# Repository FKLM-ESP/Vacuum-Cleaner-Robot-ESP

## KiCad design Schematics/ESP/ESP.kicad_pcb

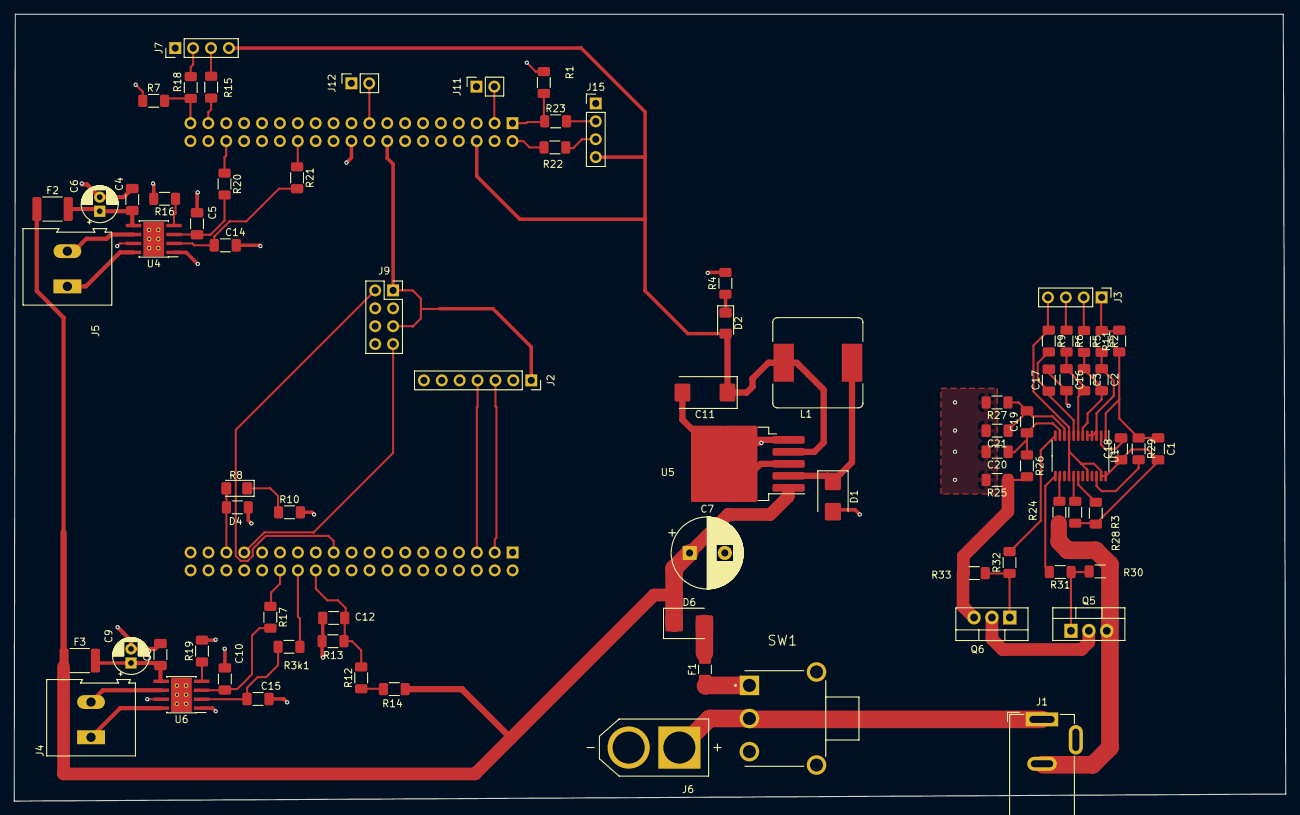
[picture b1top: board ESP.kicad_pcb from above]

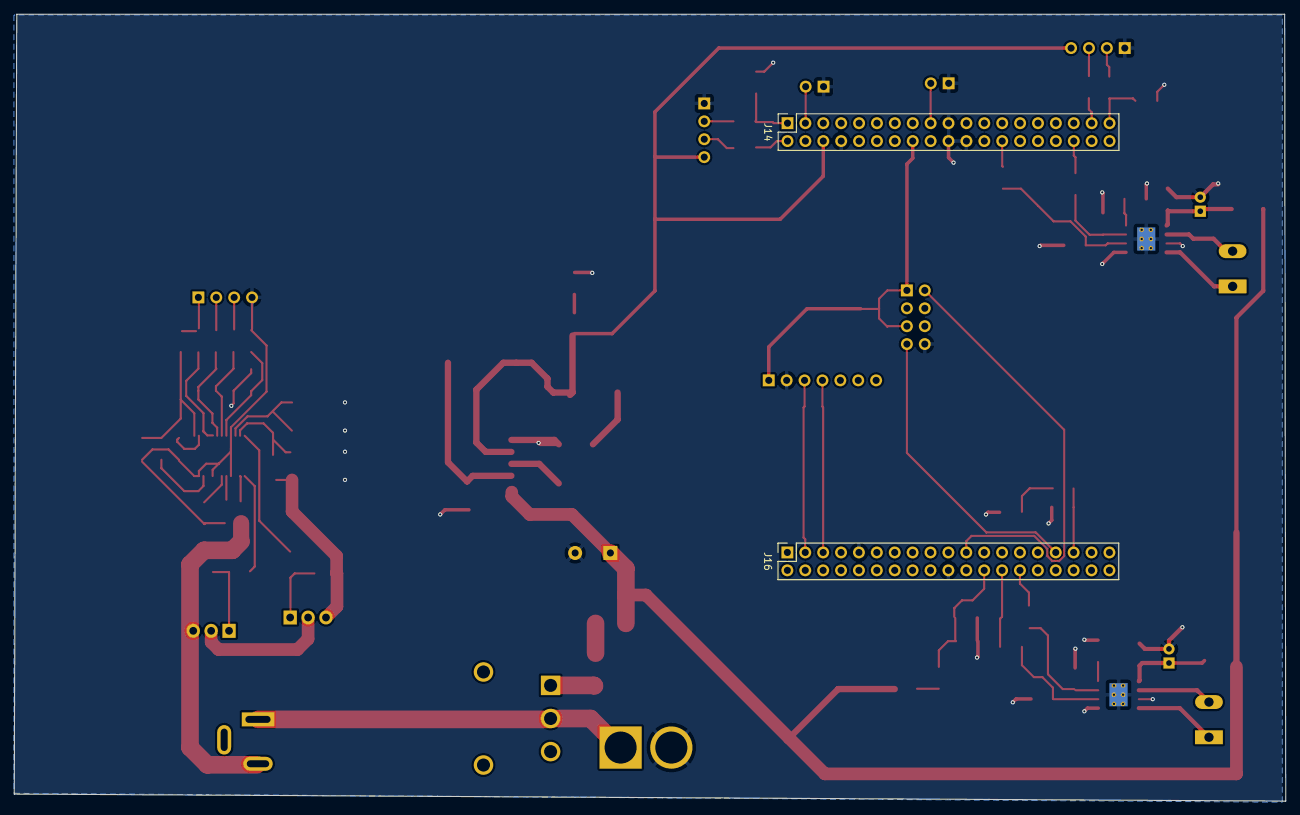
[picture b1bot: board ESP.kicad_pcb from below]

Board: 2 copper layers, 180.5 x 111.7 mm, 82 parts (2 on the bottom side), 65 nets.

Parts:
C1, C18, C20, C21: 1µF; C_1206_3216Metric_Pad1.33x1.80mm_HandSolder
C2, C3, C4, C8, C16, C17, C19: 100nF; C_1206_3216Metric_Pad1.33x1.80mm_HandSolder
C5, C10, C12, C14, C15: 10n; C_1206_3216Metric_Pad1.33x1.80mm_HandSolder
C6, C9: 47u; CP_Radial_D5.0mm_P2.00mm
C7: 680u; CP_Radial_D10.0mm_P5.00mm
C11: 220u; CP_EIA-7343-31_Kemet-D_Pad2.25x2.55mm_HandSolder
D1, D6: PMEG045V050EPDZ; D_SMB
D2, D4: GREEN; LED_1206_3216Metric_Pad1.42x1.75mm_HandSolder
F1: 5A; Fuse_1206_3216Metric_Pad1.42x1.75mm_HandSolder
F2, F3: 1.6A; Fuse_1812_4532Metric_Pad1.30x3.40mm_HandSolder
J1: Barrel_Jack; BarrelJack_GCT_DCJ200-10-A_Horizontal
J2: IMU; PinSocket_1x07_P2.54mm_Vertical
J3: Battery charger; PinHeader_1x04_P2.54mm_Vertical
J4: Motor A; TerminalBlock_Altech_AK300-2_P5.00mm
J5: Motor B; TerminalBlock_Altech_AK300-2_P5.00mm
J6: XT60-M; AMASS_XT60-M
J7: UltraSonic A; PinHeader_1x04_P2.54mm_Vertical
J9: ESP; PinSocket_2x04_P2.54mm_Vertical
J11: Bumper 1; PinSocket_1x02_P2.54mm_Vertical
J12: Bumper 2; PinSocket_1x02_P2.54mm_Vertical
J14, J16: Conn_02x19_Odd_Even; PinSocket_2x19_P2.54mm_Vertical
J15: UltraSconic B; PinHeader_1x04_P2.54mm_Vertical
L1: 33uH; L_Bourns_SRR1260
Q5, Q6: IRLB8721PBF; TO-220-3_Vertical
R1, R3, R7, R8, R12, R14, R15, R18, R22, R23: 10k; R_1206_3216Metric_Pad1.30x1.75mm_HandSolder
R2, R5, R6, R9, R26, R27: 100; R_1206_3216Metric_Pad1.30x1.75mm_HandSolder
R3k1, R17, R20, R21: 3.3; R_1206_3216Metric_Pad1.30x1.75mm_HandSolder
R4, R10, R11, R31: 1k; R_1206_3216Metric_Pad1.30x1.75mm_HandSolder
R13: 6.2k; R_1206_3216Metric_Pad1.30x1.75mm_HandSolder
R16, R19: 39k; R_1206_3216Metric_Pad1.30x1.75mm_HandSolder
R24: 450K; R_1206_3216Metric_Pad1.30x1.75mm_HandSolder
R25: 10m; R_1206_3216Metric_Pad1.30x1.75mm_HandSolder
R28: 100K; R_1206_3216Metric_Pad1.30x1.75mm_HandSolder
R29: 10K; R_1206_3216Metric_Pad1.30x1.75mm_HandSolder
R30: 3.3M; R_1206_3216Metric_Pad1.30x1.75mm_HandSolder
R32: 4.5K; R_1206_3216Metric_Pad1.30x1.75mm_HandSolder
R33: 1M; R_1206_3216Metric_Pad1.30x1.75mm_HandSolder
SW1: SW_SPDT; SW_500SSP1S1M6QEA
U1: BQ7791500PWT; TSSOP-24_4.4x7.8mm_P0.65mm
U4, U6: DRV8871DDA; Texas_HTSOP-8-1EP_3.9x4.9mm_P1.27mm_EP2.95x4.9mm_Mask2.4x3.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
U5: LM2596S-5; TO-263-5_TabPin3

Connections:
+3.3V: J2.1, J9.1, J9.5, J14.16
+5V: C11.1, D2.2 (A), J7.4, J14.6, J15.4, L1.2, U5.4 (FB)
+12V: C7.1, D6.1 (K), F2.1, F3.1, R14.1, U5.1 (VIN)
Battery level: C12.1, J16.24, R12.2, R13.1
Battery+: J1.1, J6.P (POS), SW1.2 (B)
Battery-: C1.2, C4.2, C5.2, C6.2, C7.2, C8.2, C9.2, C10.2, C11.2, C12.2, C14.2, C15.2, C16.2, C17.2, C18.1, C20.2, C21.2, D1.2 (A), J2.2, J3.4, J6.N (NEG), J7.1, J9.8, J11.1, J12.1, J14.8, J14.19, J14.20, J14.22, J15.1, J16.9, J16.20, R1.1, R3.2, R4.2, R7.1, R8.2, R9.1, R10.2, R13.2, R16.2, R19.2, R25.2, R27.2, R28.2, U1.9 (VSS), U1.16 (CBI), U1.20 (CCFG), U1.23 (CTRC), U1.24 (CTRD), U4.1 (GND), U4.7 (GND), U4.9 (GND), U5.3 (GND), U5.5 (~ON/OFF), U6.1 (GND), U6.7 (GND), U6.9 (GND)
Bumper Button 1: J11.2, J14.3
Bumper Button 2: J12.2, J14.17
CHG: R31.2, U1.13 (CHG)
Cell1+: J3.3, R6.1
Cell2+: J3.2, R5.1
Cell3+: J3.1, R2.1, R11.2
DSG: R32.2, U1.12 (DSG)
Echo A: J14.37, R7.2, R18.1
Echo B: J14.1, R1.2, R23.1
Fan Signal: D4.2 (A), J16.33, R8.1
InputA1: J16.28, R17.1
InputA2: J16.26, R3k1.1
InputB1: J14.34, R20.1
InputB2: J14.26, R21.1
MotorA+: J4.2, U6.6 (OUT1)
MotorA-: J4.1, U6.8 (OUT2)
MotorB+: J5.2, U4.6 (OUT1)
MotorB-: J5.1, U4.8 (OUT2)
unnamed: D1.1 (K), L1.1, U5.2 (OUT)
unnamed: D2.1 (K), R4.1
unnamed: D4.1 (K), R10.1
unnamed: D6.2 (A), F1.2
unnamed: J7.2, R18.2
unnamed: J7.3, R15.2
unnamed: J15.2, R23.2
unnamed: J15.3, R22.2
unnamed: J2.3, J16.3
unnamed: J2.4, J16.5
unnamed: Q5.2 (D), Q6.2 (D)
unnamed: Q5.1 (G), R30.2, R31.1
unnamed: Q6.1 (G), R32.1, R33.2
unnamed: Q6.3 (S), R25.1, R26.2, R33.1
unnamed: R12.1, R14.2
unnamed: F1.1, SW1.1 (A)
unnamed: C18.2, U1.2 (AVDD)
unnamed: R24.1, U1.14 (LD)
unnamed: R28.1, U1.17 (OCDP)
unnamed: R29.2, U1.22 (PRES)
unnamed: C19.1, C20.1, R26.1, U1.11 (SRN)
unnamed: C19.2, C21.1, R27.1, U1.10 (SRP)
unnamed: R3.1, U1.18 (TS)
unnamed: C17.1, R9.2, U1.8 (VC0)
unnamed: C3.2, C16.1, R6.2, U1.7 (VC1)
unnamed: C2.2, C3.1, R5.2, U1.6 (VC2)
unnamed: C2.1, R2.2, U1.3 (VC5), U1.4 (VC4), U1.5 (VC3)
unnamed: C1.1, R11.1, R29.1, U1.1 (VDD)
unnamed: R16.1, U4.4 (ILIM)
unnamed: C5.1, R20.2, U4.3 (IN1)
unnamed: C14.1, R21.2, U4.2 (IN2)
unnamed: C4.1, C6.1, F2.2, U4.5 (VM)
unnamed: R19.1, U6.4 (ILIM)
unnamed: C10.1, R17.2, U6.3 (IN1)
unnamed: C15.1, R3k1.2, U6.2 (IN2)
unnamed: C8.1, C9.1, F3.2, U6.5 (VM)
P-: J1.2, Q5.3 (S), R24.2, R30.1
RX: J9.7, J16.31
TX: J9.2, J16.21
Trig A: J14.35, R15.1
Trig B: J14.2, R22.1

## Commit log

2023-02-27 added NuceloBoard Schematics
2023-03-10 Create empty
2023-03-10 Everything is in ESP revised and updated by khalil
2023-03-11 Added fuses and not connected resistors
2023-03-12 small tweaks
2023-03-12 Tried to add connectors for all peripherals
2023-03-13 Add files via upload
    - Added comments to the voltage regulator, Fan driver, and battery protection
    - Added links to digikey pages of components (voltage regulator, Fan driver, and battery IC)
    - Added Footprints to components (voltage regulator, Fan driver, and battery protection IC)
    - Replaced Schottky diode in voltage regulator with one that is currently in stock
    - Changed the value of the pull-down resistor in the Fan driver to 10K
    - Renamed some labels to make more sense:
2023-03-14 Schematics
2023-03-14 Added footprints, IR pins and bill of materials-Khalil
2023-03-15 changed values of resistors in voltage divider
2023-03-15 Added bill of material
2023-03-15 added excel
2023-03-15 Added resistors to BOM
2023-03-15 Added stuff to BOM
2023-03-15 Added some connectors
2023-03-15 NewBOM
2023-03-15 newer BOM
2023-03-15 Updated BOM
2023-03-15 Added bumpers
2023-03-15 Final update on BOM
2023-03-18 Khalil Working on PCB
2023-03-18 Can Pull
2023-03-19 Dont pull khalil working on pcb
2023-03-19 fixed BOM
2023-03-19 Dont Pull
2023-03-19 some pcb changes
2023-03-20 Can't Pull
2023-03-20 Changed schematics and PCB for shield
2023-03-25 PCB layout done no wiring
2023-03-25 PCB layout done w/wiring only charging part remaining
2023-03-27 did some stuff
2023-03-27 changed fuse and regulator output diode
2023-03-27 lots of stuff
2023-03-27 generated new BOM
2023-03-27 added esp32 connected
2023-03-29 Added column name
2023-03-29 Removed needless info from bom
2023-03-29 Checking excel showcase in git
2023-04-03 charging IC PCB and cleanup
2023-04-03 charging IC PCB spacing cleanup
2023-04-12 Fixed and separate BOMs
2023-04-13 removed fan related stuff
2023-04-16 fixed 3.3v for IMU
2023-04-16 fixed cell balancing speed
2023-04-16 Added footprints for battery input and battery charger with BOM updates
2023-04-18 bom reviewed
2023-04-18 Updated BOM (hopefully for the last time)
2023-04-21 Added exported bom from digikey
2023-04-21 Updated exported bom to have correct headers
2023-05-06 fixed power tracks
2023-05-09 updated footprints
2023-07-16 PCB and Schematics update for future usage
